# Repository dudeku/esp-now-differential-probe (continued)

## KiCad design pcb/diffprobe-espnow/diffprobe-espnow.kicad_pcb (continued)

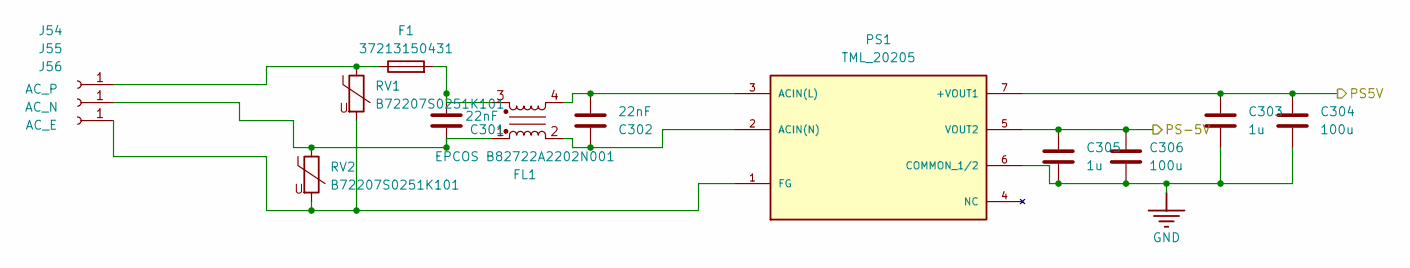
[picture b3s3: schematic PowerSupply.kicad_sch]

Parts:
C301, C302: 22nF; C_Rect_L13.0mm_W4.0mm_P10.00mm_FKS3_FKP3_MKS4
C303, C305: 1u; C_0603_1608Metric
C304, C306: 100u; CP_Elec_10x12.5
F1: 37213150431; Fuse_Littelfuse_372_D8.50mm
FL1: EPCOS B82722A2202N001; Choke_EPCOS_B82722A
J54: AC_P; Pin_D1.4mm_L8.5mm_W2.8mm_FlatFork
J55: AC_N; Pin_D1.4mm_L8.5mm_W2.8mm_FlatFork
J56: AC_E; Pin_D1.4mm_L8.5mm_W2.8mm_FlatFork
PS1: TML_20205; CONV_TML_20205; PARTREV April 7,2021
RV1, RV2: B72207S0251K101; RV_Disc_D9mm_W4.2mm_P5mm

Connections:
/PS5V: C303.1, C304.1, PS1.7 (+VOUT1); also elsewhere on the board
/PS-5V: C305.1, C306.1, PS1.5 (VOUT2); also elsewhere on the board
GND: C303.2, C304.2, C305.2, C306.2, PS1.6 (COMMON_1/2); also elsewhere on the board
unnamed: C301.2, F1.2, FL1.3
unnamed: F1.1, J54.1, RV1.1
unnamed: C301.1, FL1.1, J55.1, RV2.1
unnamed: J56.1, PS1.1 (FG), RV1.2, RV2.2
unnamed: C302.2, FL1.4, PS1.3 (ACIN(L))
unnamed: C302.1, FL1.2, PS1.2 (ACIN(N))

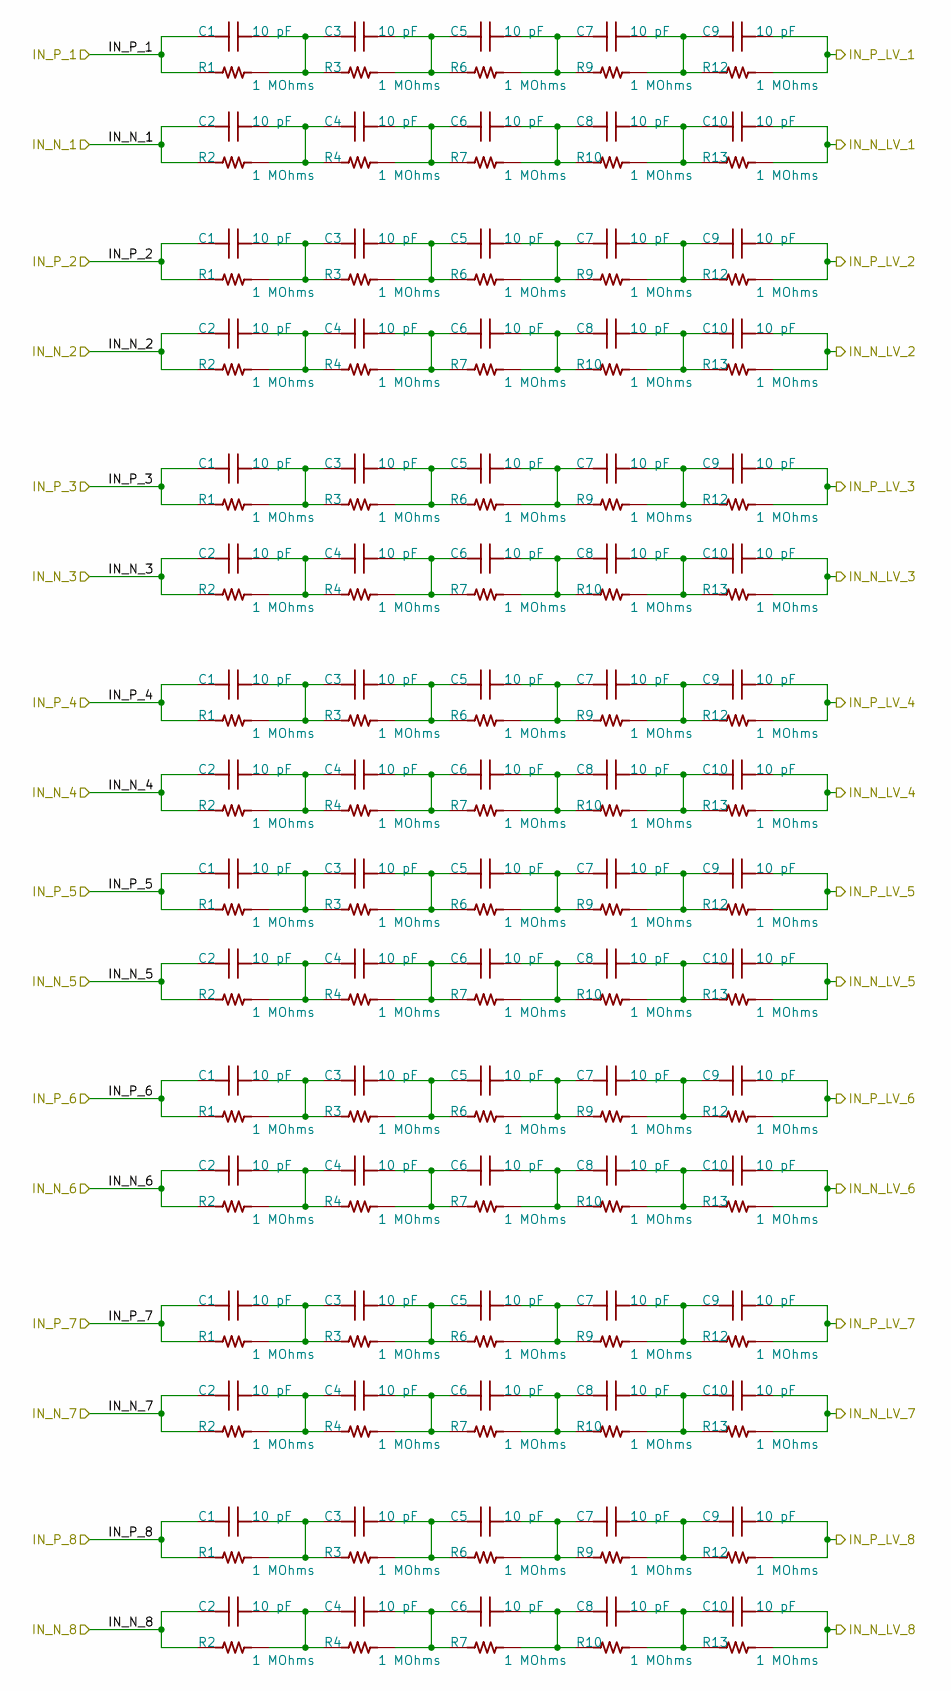
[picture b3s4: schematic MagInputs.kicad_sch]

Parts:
C1, C2, C3, C4, C5, C6, C7, C8, C9, C10: 10 pF; C_1206_3216Metric; TOLERANCE ±5%; VOLTAGE - RATED 500V; PART NUMBER CC1206JRNPOBBN100
R1, R2, R3, R4, R6, R7, R9, R10, R12, R13: 1 MOhms; R_1206_3216Metric; RATINGS AEC-Q200; TOLERANCE ±0.1%; PART NUMBER RNCS1206BKE1M00

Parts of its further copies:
C501, C502, C503, C504, C505, C506, C507, C508, C509, C510, C511, C512, C513, C514, C515, C516, C517, C518, C519, C520, C521, C522, C523, C524, C525, C526, C527, C528, C529, C530, C531, C532, C533, C534, C535, C536, C537, C538, C539, C540, C541, C542, C543, C544, C545, C546, C547, C548, C549, C550, C551, C552, C553, C554, C555, C556, C557, C558, C559, C560, C561, C562, C563, C564, C565, C566, C567, C568, C569, C570, C571, C572, C573, C574, C575, C576, C577, C578, C579, C580, C581, C582, C583, C584, C585, C586, C587, C588, C589, C590, C591, C592, C593, C594, C595, C596, C597, C598, C599, C600, C601, C602, C603, C604, C605, C606, C607, C608, C609, C610, C611, C612, C613, C614, C615, C616, C617, C618, C619, C620, C621, C622, C623, C624, C625, C626, C627, C628, C629, C630, C631, C632, C633, C634, C635, C636, C637, C638, C639, C640, C641, C642, C643, C644, C645, C646, C647, C648, C649, C650, C651, C652, C653, C654, C655, C656, C657, C658, C659, C660: 10 pF; C_1206_3216Metric; TOLERANCE ±5%; VOLTAGE - RATED 500V; PART NUMBER CC1206JRNPOBBN100
R501, R502, R503, R504, R505, R506, R507, R508, R509, R510, R511, R512, R513, R514, R515, R516, R517, R518, R519, R520, R521, R522, R523, R524, R525, R526, R527, R528, R529, R530, R531, R532, R533, R534, R535, R536, R537, R538, R539, R540, R541, R542, R543, R544, R545, R546, R547, R548, R549, R550, R551, R552, R553, R554, R555, R556, R557, R558, R559, R560, R561, R562, R563, R564, R565, R566, R567, R568, R569, R570, R571, R572, R573, R574, R575, R576, R577, R578, R579, R580, R581, R582, R583, R584, R585, R586, R587, R588, R589, R590, R591, R592, R593, R594, R595, R596, R597, R598, R599, R600, R601, R602, R603, R604, R605, R606, R607, R608, R609, R610, R611, R612, R613, R614, R615, R616, R617, R618, R619, R620, R621, R622, R623, R624, R625, R626, R627, R628, R629, R630, R631, R632, R633, R634, R635, R636, R637, R638, R639, R640, R641, R642, R643, R644, R645, R646, R647, R648, R649, R650, R651, R652, R653, R654, R655, R656, R657, R658, R659, R660: 1 MOhms; R_1206_3216Metric; RATINGS AEC-Q200; TOLERANCE ±0.1%; PART NUMBER RNCS1206BKE1M00

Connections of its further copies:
/8diffInputs1/IN_N_1: C586.1, R586.1; also elsewhere on the board
/8diffInputs1/IN_N_2: C596.1, R596.1; also elsewhere on the board
/8diffInputs1/IN_N_3: C606.1, R606.1; also elsewhere on the board
/8diffInputs1/IN_N_4: C616.1, R616.1; also elsewhere on the board
/8diffInputs1/IN_N_5: C626.1, R626.1; also elsewhere on the board
/8diffInputs1/IN_N_6: C636.1, R636.1; also elsewhere on the board
/8diffInputs1/IN_N_7: C646.1, R646.1; also elsewhere on the board
/8diffInputs1/IN_N_8: C656.1, R656.1; also elsewhere on the board
/8diffInputs1/IN_N_LV_1: C590.2, R590.2; also elsewhere on the board
/8diffInputs1/IN_N_LV_2: C600.2, R600.2; also elsewhere on the board
/8diffInputs1/IN_N_LV_3: C610.2, R610.2; also elsewhere on the board
/8diffInputs1/IN_N_LV_4: C620.2, R620.2; also elsewhere on the board
/8diffInputs1/IN_N_LV_5: C630.2, R630.2; also elsewhere on the board
/8diffInputs1/IN_N_LV_6: C640.2, R640.2; also elsewhere on the board
/8diffInputs1/IN_N_LV_7: C650.2, R650.2; also elsewhere on the board
/8diffInputs1/IN_N_LV_8: C660.2, R660.2; also elsewhere on the board
/8diffInputs1/IN_P_1: C581.1, R581.1; also elsewhere on the board
/8diffInputs1/IN_P_2: C591.1, R591.1; also elsewhere on the board
/8diffInputs1/IN_P_3: C601.1, R601.1; also elsewhere on the board
/8diffInputs1/IN_P_4: C611.1, R611.1; also elsewhere on the board
/8diffInputs1/IN_P_5: C621.1, R621.1; also elsewhere on the board
/8diffInputs1/IN_P_6: C631.1, R631.1; also elsewhere on the board
/8diffInputs1/IN_P_7: C641.1, R641.1; also elsewhere on the board
/8diffInputs1/IN_P_8: C651.1, R651.1; also elsewhere on the board
/8diffInputs1/IN_P_LV_1: C585.2, R585.2; also elsewhere on the board
/8diffInputs1/IN_P_LV_2: C595.2, R595.2; also elsewhere on the board
/8diffInputs1/IN_P_LV_3: C605.2, R605.2; also elsewhere on the board
/8diffInputs1/IN_P_LV_4: C615.2, R615.2; also elsewhere on the board
/8diffInputs1/IN_P_LV_5: C625.2, R625.2; also elsewhere on the board
/8diffInputs1/IN_P_LV_6: C635.2, R635.2; also elsewhere on the board
/8diffInputs1/IN_P_LV_7: C645.2, R645.2; also elsewhere on the board
/8diffInputs1/IN_P_LV_8: C655.2, R655.2; also elsewhere on the board
/8diffInputs/IN_N_1: C506.1, R506.1; also elsewhere on the board
/8diffInputs/IN_N_2: C516.1, R516.1; also elsewhere on the board
/8diffInputs/IN_N_3: C526.1, R526.1; also elsewhere on the board
/8diffInputs/IN_N_4: C536.1, R536.1; also elsewhere on the board
/8diffInputs/IN_N_5: C546.1, R546.1; also elsewhere on the board
/8diffInputs/IN_N_6: C556.1, R556.1; also elsewhere on the board
/8diffInputs/IN_N_7: C566.1, R566.1; also elsewhere on the board
/8diffInputs/IN_N_8: C576.1, R576.1; also elsewhere on the board
/8diffInputs/IN_N_LV_1: C510.2, R510.2; also elsewhere on the board
/8diffInputs/IN_N_LV_2: C520.2, R520.2; also elsewhere on the board
/8diffInputs/IN_N_LV_3: C530.2, R530.2; also elsewhere on the board
/8diffInputs/IN_N_LV_4: C540.2, R540.2; also elsewhere on the board
/8diffInputs/IN_N_LV_5: C550.2, R550.2; also elsewhere on the board
/8diffInputs/IN_N_LV_6: C560.2, R560.2; also elsewhere on the board
/8diffInputs/IN_N_LV_7: C570.2, R570.2; also elsewhere on the board
/8diffInputs/IN_N_LV_8: C580.2, R580.2; also elsewhere on the board
/8diffInputs/IN_P_1: C501.1, R501.1; also elsewhere on the board
/8diffInputs/IN_P_2: C511.1, R511.1; also elsewhere on the board
/8diffInputs/IN_P_3: C521.1, R521.1; also elsewhere on the board
/8diffInputs/IN_P_4: C531.1, R531.1; also elsewhere on the board
/8diffInputs/IN_P_5: C541.1, R541.1; also elsewhere on the board
/8diffInputs/IN_P_6: C551.1, R551.1; also elsewhere on the board
/8diffInputs/IN_P_7: C561.1, R561.1; also elsewhere on the board
/8diffInputs/IN_P_8: C571.1, R571.1; also elsewhere on the board
/8diffInputs/IN_P_LV_1: C505.2, R505.2; also elsewhere on the board
/8diffInputs/IN_P_LV_2: C515.2, R515.2; also elsewhere on the board
/8diffInputs/IN_P_LV_3: C525.2, R525.2; also elsewhere on the board
/8diffInputs/IN_P_LV_4: C535.2, R535.2; also elsewhere on the board
/8diffInputs/IN_P_LV_5: C545.2, R545.2; also elsewhere on the board
/8diffInputs/IN_P_LV_6: C555.2, R555.2; also elsewhere on the board
/8diffInputs/IN_P_LV_7: C565.2, R565.2; also elsewhere on the board
/8diffInputs/IN_P_LV_8: C575.2, R575.2; also elsewhere on the board
unnamed: C501.2, C502.1, R501.2, R502.1
unnamed: C502.2, C503.1, R502.2, R503.1
unnamed: C503.2, C504.1, R503.2, R504.1
unnamed: C504.2, C505.1, R504.2, R505.1
unnamed: C506.2, C507.1, R506.2, R507.1
unnamed: C507.2, C508.1, R507.2, R508.1
unnamed: C508.2, C509.1, R508.2, R509.1
unnamed: C509.2, C510.1, R509.2, R510.1
unnamed: C511.2, C512.1, R511.2, R512.1
unnamed: C512.2, C513.1, R512.2, R513.1
unnamed: C513.2, C514.1, R513.2, R514.1
unnamed: C514.2, C515.1, R514.2, R515.1
unnamed: C516.2, C517.1, R516.2, R517.1
unnamed: C517.2, C518.1, R517.2, R518.1
unnamed: C518.2, C519.1, R518.2, R519.1
unnamed: C519.2, C520.1, R519.2, R520.1
unnamed: C521.2, C522.1, R521.2, R522.1
unnamed: C522.2, C523.1, R522.2, R523.1
unnamed: C523.2, C524.1, R523.2, R524.1
unnamed: C524.2, C525.1, R524.2, R525.1
unnamed: C526.2, C527.1, R526.2, R527.1
unnamed: C527.2, C528.1, R527.2, R528.1
unnamed: C528.2, C529.1, R528.2, R529.1
unnamed: C529.2, C530.1, R529.2, R530.1
unnamed: C531.2, C532.1, R531.2, R532.1
unnamed: C532.2, C533.1, R532.2, R533.1
unnamed: C533.2, C534.1, R533.2, R534.1
unnamed: C534.2, C535.1, R534.2, R535.1
unnamed: C536.2, C537.1, R536.2, R537.1
unnamed: C537.2, C538.1, R537.2, R538.1
unnamed: C538.2, C539.1, R538.2, R539.1
unnamed: C539.2, C540.1, R539.2, R540.1
unnamed: C541.2, C542.1, R541.2, R542.1
unnamed: C542.2, C543.1, R542.2, R543.1
unnamed: C543.2, C544.1, R543.2, R544.1
unnamed: C544.2, C545.1, R544.2, R545.1
unnamed: C546.2, C547.1, R546.2, R547.1
unnamed: C547.2, C548.1, R547.2, R548.1
unnamed: C548.2, C549.1, R548.2, R549.1
unnamed: C549.2, C550.1, R549.2, R550.1
unnamed: C551.2, C552.1, R551.2, R552.1
unnamed: C552.2, C553.1, R552.2, R553.1
unnamed: C553.2, C554.1, R553.2, R554.1
unnamed: C554.2, C555.1, R554.2, R555.1
unnamed: C556.2, C557.1, R556.2, R557.1
unnamed: C557.2, C558.1, R557.2, R558.1
unnamed: C558.2, C559.1, R558.2, R559.1
unnamed: C559.2, C560.1, R559.2, R560.1
unnamed: C561.2, C562.1, R561.2, R562.1
unnamed: C562.2, C563.1, R562.2, R563.1
unnamed: C563.2, C564.1, R563.2, R564.1
unnamed: C564.2, C565.1, R564.2, R565.1
unnamed: C566.2, C567.1, R566.2, R567.1
unnamed: C567.2, C568.1, R567.2, R568.1
unnamed: C568.2, C569.1, R568.2, R569.1
unnamed: C569.2, C570.1, R569.2, R570.1
unnamed: C571.2, C572.1, R571.2, R572.1
unnamed: C572.2, C573.1, R572.2, R573.1
unnamed: C573.2, C574.1, R573.2, R574.1
unnamed: C574.2, C575.1, R574.2, R575.1
unnamed: C576.2, C577.1, R576.2, R577.1
unnamed: C577.2, C578.1, R577.2, R578.1
unnamed: C578.2, C579.1, R578.2, R579.1
unnamed: C579.2, C580.1, R579.2, R580.1
unnamed: C581.2, C582.1, R581.2, R582.1
unnamed: C582.2, C583.1, R582.2, R583.1
unnamed: C583.2, C584.1, R583.2, R584.1
unnamed: C584.2, C585.1, R584.2, R585.1
unnamed: C586.2, C587.1, R586.2, R587.1
unnamed: C587.2, C588.1, R587.2, R588.1
unnamed: C588.2, C589.1, R588.2, R589.1
unnamed: C589.2, C590.1, R589.2, R590.1
unnamed: C591.2, C592.1, R591.2, R592.1
unnamed: C592.2, C593.1, R592.2, R593.1
unnamed: C593.2, C594.1, R593.2, R594.1
unnamed: C594.2, C595.1, R594.2, R595.1
unnamed: C596.2, C597.1, R596.2, R597.1
unnamed: C597.2, C598.1, R597.2, R598.1
unnamed: C598.2, C599.1, R598.2, R599.1
unnamed: C599.2, C600.1, R599.2, R600.1
unnamed: C601.2, C602.1, R601.2, R602.1
unnamed: C602.2, C603.1, R602.2, R603.1
unnamed: C603.2, C604.1, R603.2, R604.1
unnamed: C604.2, C605.1, R604.2, R605.1
unnamed: C606.2, C607.1, R606.2, R607.1
unnamed: C607.2, C608.1, R607.2, R608.1
unnamed: C608.2, C609.1, R608.2, R609.1
unnamed: C609.2, C610.1, R609.2, R610.1
unnamed: C611.2, C612.1, R611.2, R612.1
unnamed: C612.2, C613.1, R612.2, R613.1
unnamed: C613.2, C614.1, R613.2, R614.1
unnamed: C614.2, C615.1, R614.2, R615.1
unnamed: C616.2, C617.1, R616.2, R617.1
unnamed: C617.2, C618.1, R617.2, R618.1
unnamed: C618.2, C619.1, R618.2, R619.1
unnamed: C619.2, C620.1, R619.2, R620.1
unnamed: C621.2, C622.1, R621.2, R622.1
unnamed: C622.2, C623.1, R622.2, R623.1
unnamed: C623.2, C624.1, R623.2, R624.1
unnamed: C624.2, C625.1, R624.2, R625.1
unnamed: C626.2, C627.1, R626.2, R627.1
unnamed: C627.2, C628.1, R627.2, R628.1
unnamed: C628.2, C629.1, R628.2, R629.1
unnamed: C629.2, C630.1, R629.2, R630.1
unnamed: C631.2, C632.1, R631.2, R632.1
unnamed: C632.2, C633.1, R632.2, R633.1
unnamed: C633.2, C634.1, R633.2, R634.1
unnamed: C634.2, C635.1, R634.2, R635.1
unnamed: C636.2, C637.1, R636.2, R637.1
unnamed: C637.2, C638.1, R637.2, R638.1
unnamed: C638.2, C639.1, R638.2, R639.1
unnamed: C639.2, C640.1, R639.2, R640.1
unnamed: C641.2, C642.1, R641.2, R642.1
unnamed: C642.2, C643.1, R642.2, R643.1
unnamed: C643.2, C644.1, R643.2, R644.1
unnamed: C644.2, C645.1, R644.2, R645.1
unnamed: C646.2, C647.1, R646.2, R647.1
unnamed: C647.2, C648.1, R647.2, R648.1
unnamed: C648.2, C649.1, R648.2, R649.1
unnamed: C649.2, C650.1, R649.2, R650.1
unnamed: C651.2, C652.1, R651.2, R652.1
unnamed: C652.2, C653.1, R652.2, R653.1
unnamed: C653.2, C654.1, R653.2, R654.1
unnamed: C654.2, C655.1, R654.2, R655.1
unnamed: C656.2, C657.1, R656.2, R657.1
unnamed: C657.2, C658.1, R657.2, R658.1
unnamed: C658.2, C659.1, R658.2, R659.1
unnamed: C659.2, C660.1, R659.2, R660.1

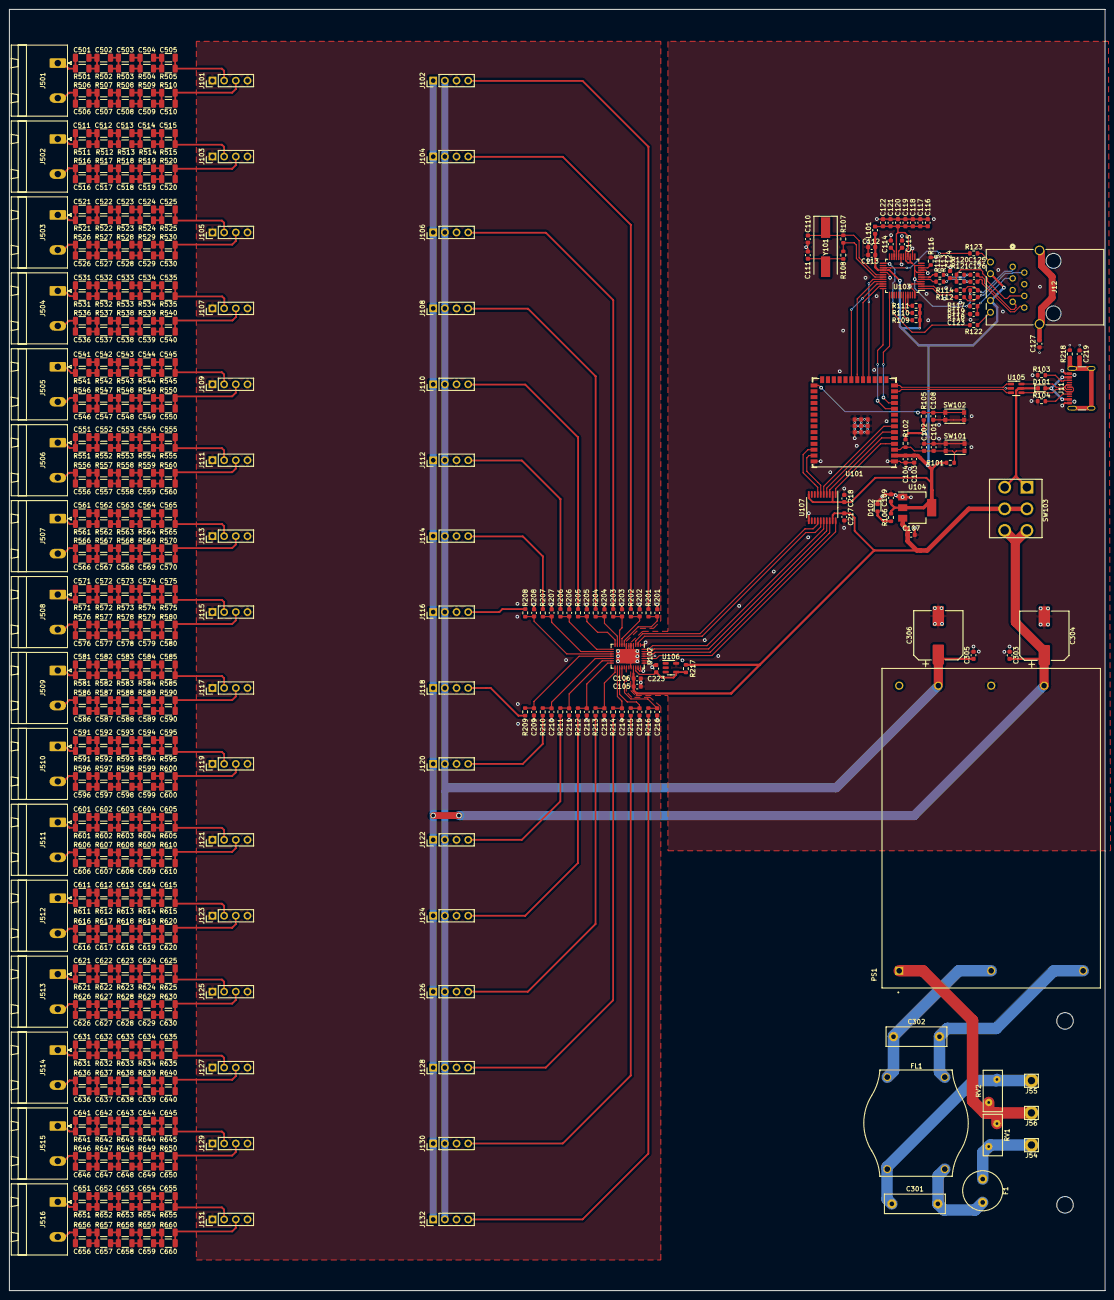
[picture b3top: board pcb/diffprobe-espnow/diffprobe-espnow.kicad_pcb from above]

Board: 2 copper layers, 238.2 x 278.6 mm, 486 parts (0 on the bottom side), 293 nets.

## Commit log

2024-12-04 readme
2024-12-04 add pcb files
2024-12-04 probe code 23-10
2024-12-04 probe code 29-11
2024-12-04 probe code 04-12
2024-12-11 test
2024-12-11 gateway code rename
2024-12-11 Revert to framework arduino-esp32 2.0.17 because of spi3 miso problem
2024-12-11 Readme update lib fixes
2024-12-11 Case DXF files
2024-12-11 Fix found for Arduino 3.x framework
2024-12-13 Per channel reading correction
2025-01-14 Added millis measurement in struct, osr changed to 256
2025-01-21 scripts to collect data
2025-01-22 working capture script and data plotting
2025-01-22 plot with smoothing
2025-01-31 clean up measurement data
2025-02-12 Merge branch 'main' of https://github.com/dudeku/esp-now-differential-probe into HEAD
    # Conflicts:
    # code/adc-tcp/.gitignore
    # code/adc-tcp/.pio/libdeps/esp32-s3-n8r8-cdc/Ethernet/src/Ethernet.h
    # code/adc-tcp/.pio/libdeps/esp32-s3-n8r8-cdc/Ethernet/src/EthernetServer.cpp
    # code/adc-tcp/.pio/libdeps/esp32-s3-n8r8-cdc/integrity.dat
    # code/adc-tcp/platformio.ini
2025-02-18 add more vias
2025-02-25 save graphs to file, new measurements
2025-02-25 cleaning
2025-03-04 new data plotted
2025-03-04 new data again
2025-03-11 added simulation, updated pcb designs
2025-03-27 KiCAD 9 update, new psu filtering and adc input signal filtering. More silkscreen writing.
2025-05-20 newest measurements
2025-06-05 new measurements
2025-11-01 update sim symbol
2025-11-01 tidying up schematics
2025-11-18 new way to split plotting all 16 graphs onto one figure
2025-11-18 fix timezone in epoch time data
2025-11-18 schematic cleanup again
